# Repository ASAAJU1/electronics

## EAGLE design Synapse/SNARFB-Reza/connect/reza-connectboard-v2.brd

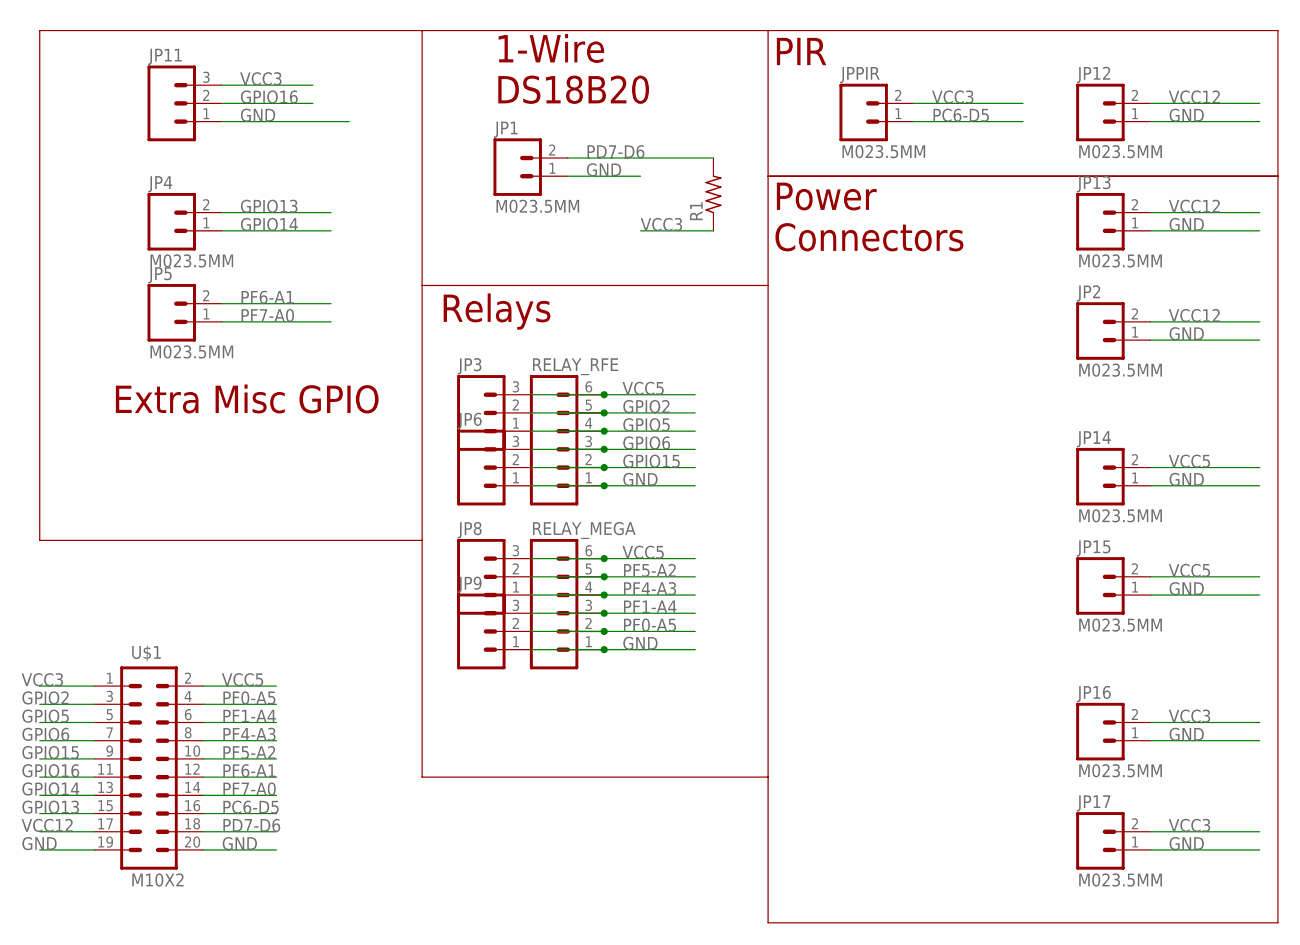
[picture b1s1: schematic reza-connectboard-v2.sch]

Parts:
JP1, JP2, JP4, JP5, JP12, JP13, JP14, JP15, JP16, JP17: M023.5MM; SCREWTERMINAL-3.5MM-2
JP3, JP6, JP8, JP9, JP11: M03SCREW; SCREWTERMINAL-3.5MM-3
JPPIR: M023.5MM; SCREWTERMINAL-3.5MM-2
R1: R-US_FLIPFLOP; 0805-THM
RELAY_MEGA: M06SIP; 1X06
RELAY_RFE: M06SIP; 1X06
U$1: M10X2; 2X10

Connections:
GND: JP1.1, JP2.1, JP6.1, JP9.1, JP11.1, JP12.1, JP13.1, JP14.1, JP15.1, JP16.1, JP17.1, RELAY_MEGA.1, RELAY_RFE.1, U$1.19, U$1.20
GPIO2: JP3.2, RELAY_RFE.5, U$1.3
GPIO5: JP3.1, RELAY_RFE.4, U$1.5
GPIO6: JP6.3, RELAY_RFE.3, U$1.7
GPIO13: JP4.2, U$1.15
GPIO14: JP4.1, U$1.13
GPIO15: JP6.2, RELAY_RFE.2, U$1.9
GPIO16: JP11.2, U$1.11
PC6-D5: JPPIR.1, U$1.16
PD7-D6: JP1.2, R1.2, U$1.18
PF0-A5: JP9.2, RELAY_MEGA.2, U$1.4
PF1-A4: JP9.3, RELAY_MEGA.3, U$1.6
PF4-A3: JP8.1, RELAY_MEGA.4, U$1.8
PF5-A2: JP8.2, RELAY_MEGA.5, U$1.10
PF6-A1: JP5.2, U$1.12
PF7-A0: JP5.1, U$1.14
VCC3: JP11.3, JP16.2, JP17.2, JPPIR.2, R1.1, U$1.1
VCC5: JP3.3, JP8.3, JP14.2, JP15.2, RELAY_MEGA.6, RELAY_RFE.6, U$1.2
VCC12: JP2.2, JP12.2, JP13.2, U$1.17

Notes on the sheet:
PIR
Power Connectors
1-Wire DS18B20
Relays
Extra Misc GPIO

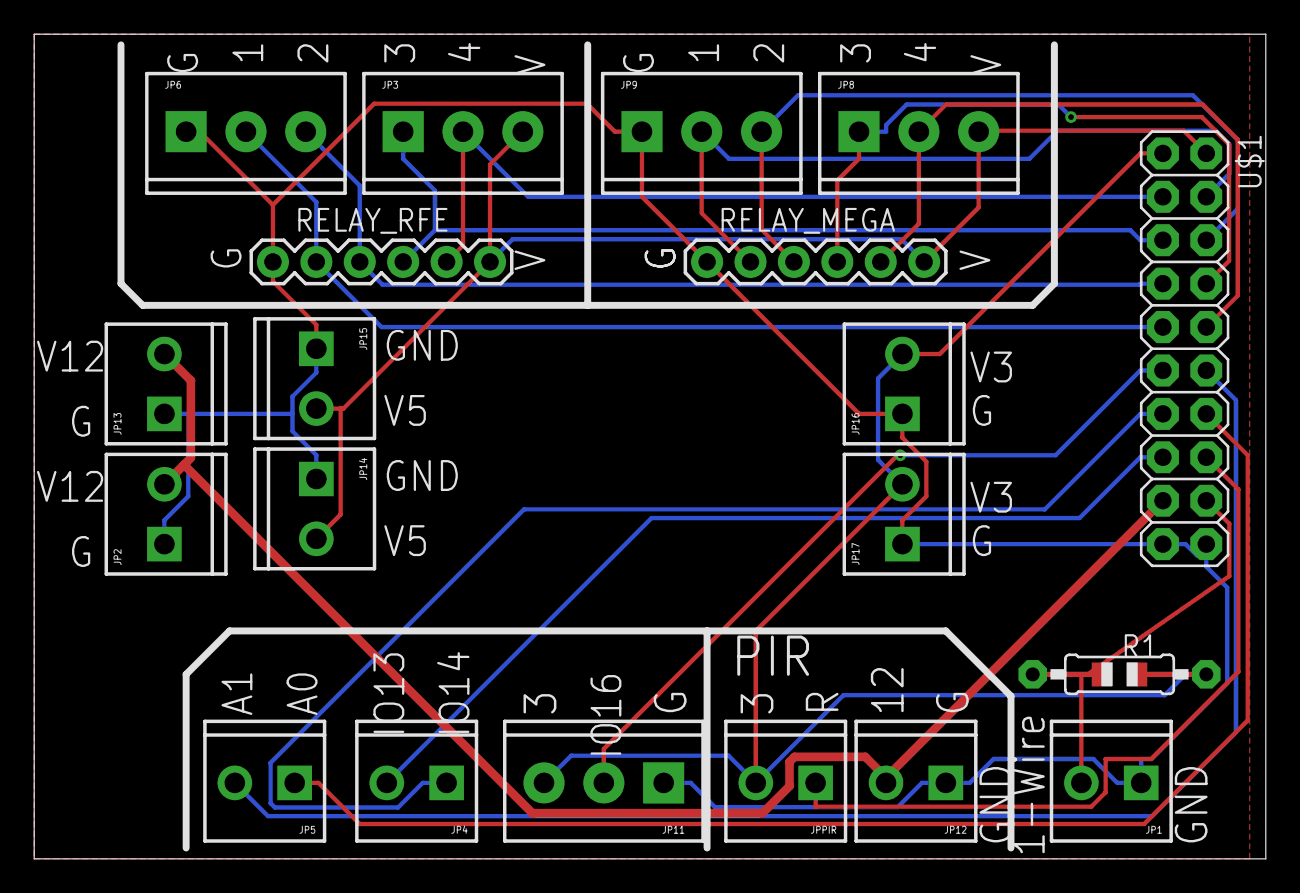
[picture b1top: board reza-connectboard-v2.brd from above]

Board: 2 copper layers, 72.1 x 48.2 mm, 21 parts (0 on the bottom side), 19 nets.

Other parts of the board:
U$2: ENVIOSYS_LOGO2

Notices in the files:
parts and their libraries:
SparkFun-Connectors: Licensing: CC v3.0 Share-Alike You are welcome to use this library for commercial purposes.
0_jc-custom-eagle6: CC BY-SA 3.0
